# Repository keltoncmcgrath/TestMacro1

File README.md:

# TestMacro1
 My first keyboard pcb, making sure I know what I'm doing.

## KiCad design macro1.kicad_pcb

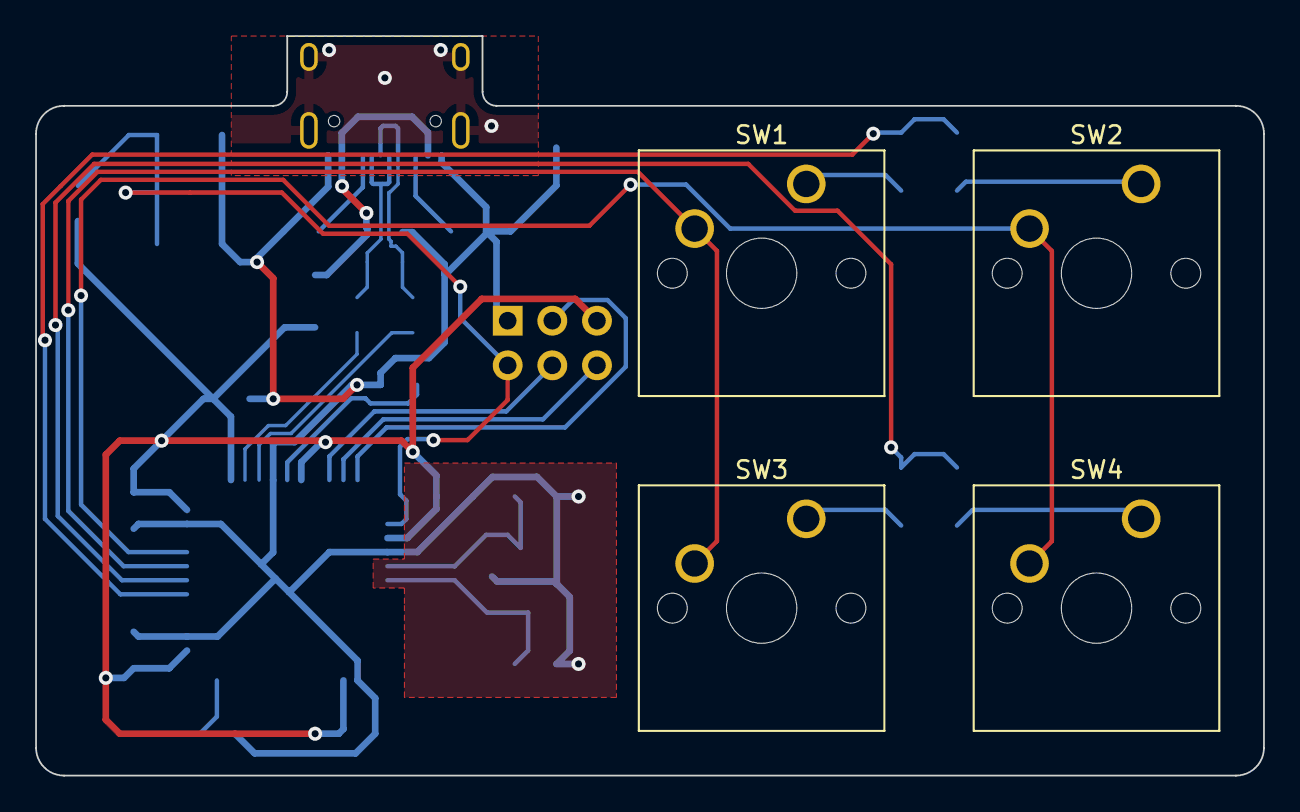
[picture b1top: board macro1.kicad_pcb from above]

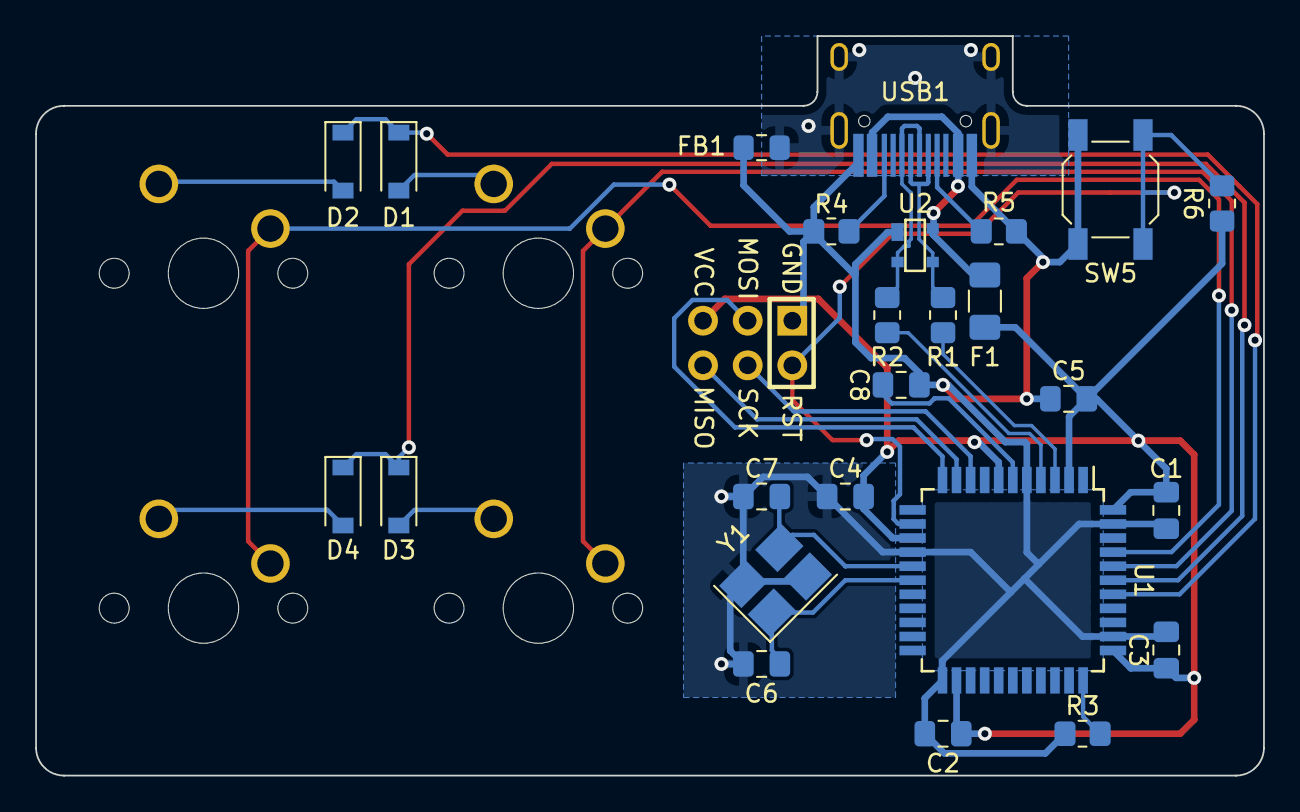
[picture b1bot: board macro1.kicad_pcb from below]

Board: 2 copper layers, 69.8 x 42.1 mm, 30 parts (26 on the bottom side), 26 nets.

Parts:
C1, C2, C3, C4: 0.1u; C_0805_2012Metric_Pad1.18x1.45mm_HandSolder
C5: 10u; C_0805_2012Metric_Pad1.18x1.45mm_HandSolder
C6, C7: 22p; C_0805_2012Metric_Pad1.18x1.45mm_HandSolder
C8: 1u; C_0805_2012Metric_Pad1.18x1.45mm_HandSolder
D1, D2, D3, D4: D; D_SOD-123
F1: 500mA; Fuse_1206_3216Metric_Pad1.42x1.75mm_HandSolder
FB1: 60@100MHz; L_0805_2012Metric_Pad1.15x1.40mm_HandSolder
J1: AVR-ISP-6; Reset_Pretty-Mask
R1, R2: 22; R_0805_2012Metric_Pad1.20x1.40mm_HandSolder
R3, R6: 10k; R_0805_2012Metric_Pad1.20x1.40mm_HandSolder
R4, R5: 5.1k; R_0805_2012Metric_Pad1.20x1.40mm_HandSolder
SW1: Macro1; SW_Cherry_MX_1.00u_PCB
SW2: Macro2; SW_Cherry_MX_1.00u_PCB
SW3: Macro3; SW_Cherry_MX_1.00u_PCB
SW4: Macro4; SW_Cherry_MX_1.00u_PCB
SW5: PUSH_RESET; SW_SPST_SKQG_WithStem
U1: ATmega32U4-A; TQFP-44_10x10mm_P0.8mm
U2: PRTR5V0U2X; SOT143B
USB1: HRO-TYPE-C-31-M-12; HRO-TYPE-C-31-M-12-HandSoldering
Y1: XTAL; Crystal_SMD_3225-4Pin_3.2x2.5mm_HandSoldering

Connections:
+5V: C1.1, C2.1, C3.1, C4.1, C5.1, F1.2, J1.2 (VCC), R6.1, U1.2 (UVCC), U1.7 (VBUS), U1.14 (VCC), U1.24 (AVCC), U1.34 (VCC), U1.44 (AVCC)
COL0: SW1.2, SW3.2, U1.40 (PF1)
COL1: SW2.2, SW4.2, U1.41 (PF0)
D+: R2.2, U1.4 (D+)
D-: R1.2, U1.3 (D-)
DN: R1.1, U2.3 (IO2), USB1.5 (DN2), USB1.7 (DN1)
DP: R2.1, U2.2 (IO1), USB1.6 (DP1), USB1.8 (DP2)
Earth: FB1.1, USB1.13 (SHIELD)
GND: C1.2, C2.2, C3.2, C4.2, C5.2, C6.2, C7.2, C8.1, FB1.2, J1.6 (GND), R3.2, R4.2, R5.2, SW5.2, U1.5 (UGND), U1.15 (GND), U1.23 (GND), U1.35 (GND), U1.43 (GND), U2.1 (GND), USB1.1 (GND), USB1.12 (GND), Y1.2, Y1.4
MISO: J1.1 (MISO), U1.10 (PB2)
MOSI: J1.4 (MOSI), U1.11 (PB3)
unnamed: R4.1, USB1.10 (CC2)
unnamed: R5.1, USB1.4 (CC1)
unnamed: D1.2 (A), SW1.1
unnamed: D2.2 (A), SW2.1
unnamed: D3.2 (A), SW3.1
unnamed: D4.2 (A), SW4.1
unnamed: C8.2, U1.6 (UCAP)
unnamed: R3.1, U1.33 (~HWB/PE2)
RESET: J1.5 (~RST), R6.2, SW5.1, U1.13 (~RESET)
ROW0: D1.1 (K), D2.1 (K), U1.38 (PF5)
ROW1: D3.1 (K), D4.1 (K), U1.39 (PF4)
SCK: J1.3 (SCK), U1.9 (PB1)
VCC: F1.1, U2.4 (VCC), USB1.2 (VBUS), USB1.11 (VBUS)
XTAL1: C6.1, U1.17 (XTAL1), Y1.1
XTAL2: C7.1, U1.16 (XTAL2), Y1.3

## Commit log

2022-06-23 Project Created
2022-06-23 Add Submodules
2022-06-23 Add Libraries and Footprints
2022-06-24 Schematic Completed
2022-06-24 First Routing: NoKeys
2022-06-24 First Route: NoKeys
2022-06-24 First Routing: Keys
2022-06-25 Finished Product 1
2022-06-26 Trial 2: MCU Schema
2022-06-27 Trial 2: Final Schema
2022-06-29 Trial 2: Components Layed Out
2022-06-29 Trial 2: Routed
2022-06-30 Trial 2: Finished Product
2022-07-23 MOSI Fix
